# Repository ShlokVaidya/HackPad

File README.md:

# HackPad

A 12-key macropad I built as my second hardware project for Stasis, designed to pair with my 60% keyboard for editing, shortcuts, media control, etc...

Hi there, this is my fully custom keypad from scratch, and I tried to keep it clean, practical, and actually buildable.

## Demo Video

<video src="./HackPad.mp4" controls width="1080">
  Your browser does not support embedded videos. You can watch the demo here: <a href="./HackPad.mp4">HackPad.mp4</a>.
</video>

[Open the demo video](./HackPad.mp4)

Note: The demo vid is working but u need to download to view it as it exceeds the 100mb Github limit. 

## Quick Project Summary

- Project: 3x4 macropad + rotary encoder
- MCU: RP2040 Zero
- Switches: 12x MX-style
- Extra input: 1x EC11 rotary encoder with push switch
- Matrix: 3 rows x 4 columns
- PCB size target: about 100mm x 65mm
- Case workflow: KiCad PCB export -> Onshape assembly -> custom bottom case + plate

## Why I Made This

I wanted a dedicated macropad next to my keyboard for common shortcuts (copy/paste, app switching, media, timeline scrubbing, etc.) and I wanted to learn the full flow:

1. keyboard layout planning
2. schematic capture
3. PCB routing
4. case CAD around real board geometry

## Features

- 12 programmable keys (MX style)
- Rotary encoder with click for volume/scroll/tool size/etc.
- RP2040-based and easy to firmware-program
- Through-hole diodes for matrix
- UART header exposed
- Custom silkscreen logos for personality

## Bill of Materials (BOM)

From [production/bom.csv](production/bom.csv):

| Item | Qty | Notes |
|---|---:|---|
| RP2040 Zero module | 1 | Main controller |
| MX-style switches | 12 | 1u keys |
| 1N4148 diodes | 12 | Matrix diodes |
| EC11 rotary encoder (with switch) | 1 | Knob + click |
| 1x4 right-angle pin header | 1 | UART / expansion |

## Design Files Included

- Schematic: [PCB/HackPad.kicad_sch](PCB/HackPad.kicad_sch)
- PCB: [PCB/HackPad.kicad_pcb](PCB/HackPad.kicad_pcb)
- KiCad project: [PCB/HackPad.kicad_pro](PCB/HackPad.kicad_pro)
- Layout JSON: [PCB/keyboard-layout.json](PCB/keyboard-layout.json)
- Plate DXF: [PCB/plate.dxf](PCB/plate.dxf)
- CAD model: [CAD/HackPad.step](CAD/HackPad.step)
- Production files:
	- [production/bom.csv](production/bom.csv)
	- [production/positions.csv](production/positions.csv)
	- [production/designators.csv](production/designators.csv)
	- [production/netlist.ipc](production/netlist.ipc)

## Firmware

KMK firmware for this board is included in:

- [firmware/kmk/code.py](firmware/kmk/code.py)
- [firmware/kmk/README.md](firmware/kmk/README.md)

It is preconfigured for the exact matrix and encoder pins used in this PCB.

## Progress Pictures

### Research

### Schematic Stage

### PCB Stage

### CAD / Case Stage

## Time Spent (from Journal)

- Research: ~0.33h
- Schematic: ~2.25h
- PCB: ~3.25h
- CAD: ~3.45h

Total logged so far: ~9.3h

## What I Learned

- Importing the actual PCB into CAD early saves a lot of pain later.
- Matrix labeling in schematic makes routing way less confusing.
- Tiny mechanical details (insert depth, nut traps, plate thickness) matter a lot more than expected.
- Silkscreen art is optional, but morale is not.

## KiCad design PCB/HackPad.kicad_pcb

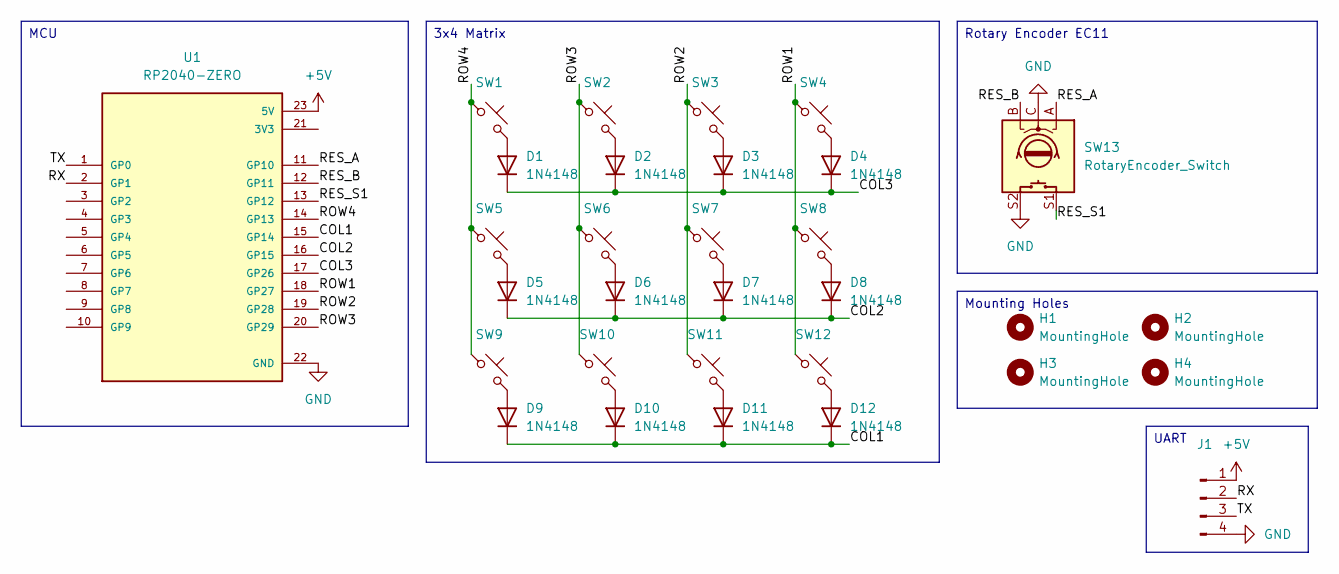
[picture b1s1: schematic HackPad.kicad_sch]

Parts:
D1, D2, D3, D4, D5, D6, D7, D8, D9, D10, D11, D12: 1N4148; D_DO-35_SOD27_P7.62mm_Horizontal
H1, H2, H3, H4: MountingHole; MountingHole_2.7mm_M2.5
J1: Conn_01x04_Pin; PinHeader_1x04_P2.54mm_Horizontal
SW1, SW2, SW3, SW4, SW5, SW6, SW7, SW8, SW9, SW10, SW11, SW12: SW_Push_45deg; SW_MX_HS_KS-2P02B01-01_1u
SW13: RotaryEncoder_Switch; RotaryEncoder_Alps_EC11E-Switch_Vertical_H20mm_MountingHoles
U1: RP2040-ZERO; MODULE_RP2040-ZERO; PARTREV NA

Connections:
+5V: J1.1, U1.23 (5V)
/COL1: D9.1 (K), D10.1 (K), D11.1 (K), D12.1 (K), U1.15 (GP14)
/COL2: D5.1 (K), D6.1 (K), D7.1 (K), D8.1 (K), U1.16 (GP15)
/COL3: D1.1 (K), D2.1 (K), D3.1 (K), D4.1 (K), U1.17 (GP26)
/RES_A: SW13.A, U1.11 (GP10)
/RES_B: SW13.B, U1.12 (GP11)
/RES_S1: SW13.S1, U1.13 (GP12)
/ROW1: SW4.1, SW8.1, SW12.1, U1.18 (GP27)
/ROW2: SW3.1, SW7.1, SW11.1, U1.19 (GP28)
/ROW3: SW2.1, SW6.1, SW10.1, U1.20 (GP29)
/ROW4: SW1.1, SW5.1, SW9.1, U1.14 (GP13)
/RX: J1.2, U1.2 (GP1)
/TX: J1.3, U1.1 (GP0)
GND: J1.4, SW13.C, SW13.S2, U1.22 (GND)
unnamed: D1.2 (A), SW1.2
unnamed: D2.2 (A), SW2.2
unnamed: D3.2 (A), SW3.2
unnamed: D4.2 (A), SW4.2
unnamed: D5.2 (A), SW5.2
unnamed: D6.2 (A), SW6.2
unnamed: D7.2 (A), SW7.2
unnamed: D8.2 (A), SW8.2
unnamed: D9.2 (A), SW9.2
unnamed: D10.2 (A), SW10.2
unnamed: D11.2 (A), SW11.2
unnamed: D12.2 (A), SW12.2

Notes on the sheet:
MCU
Mounting Holes
3x4 Matrix
UART
Rotary Encoder EC11

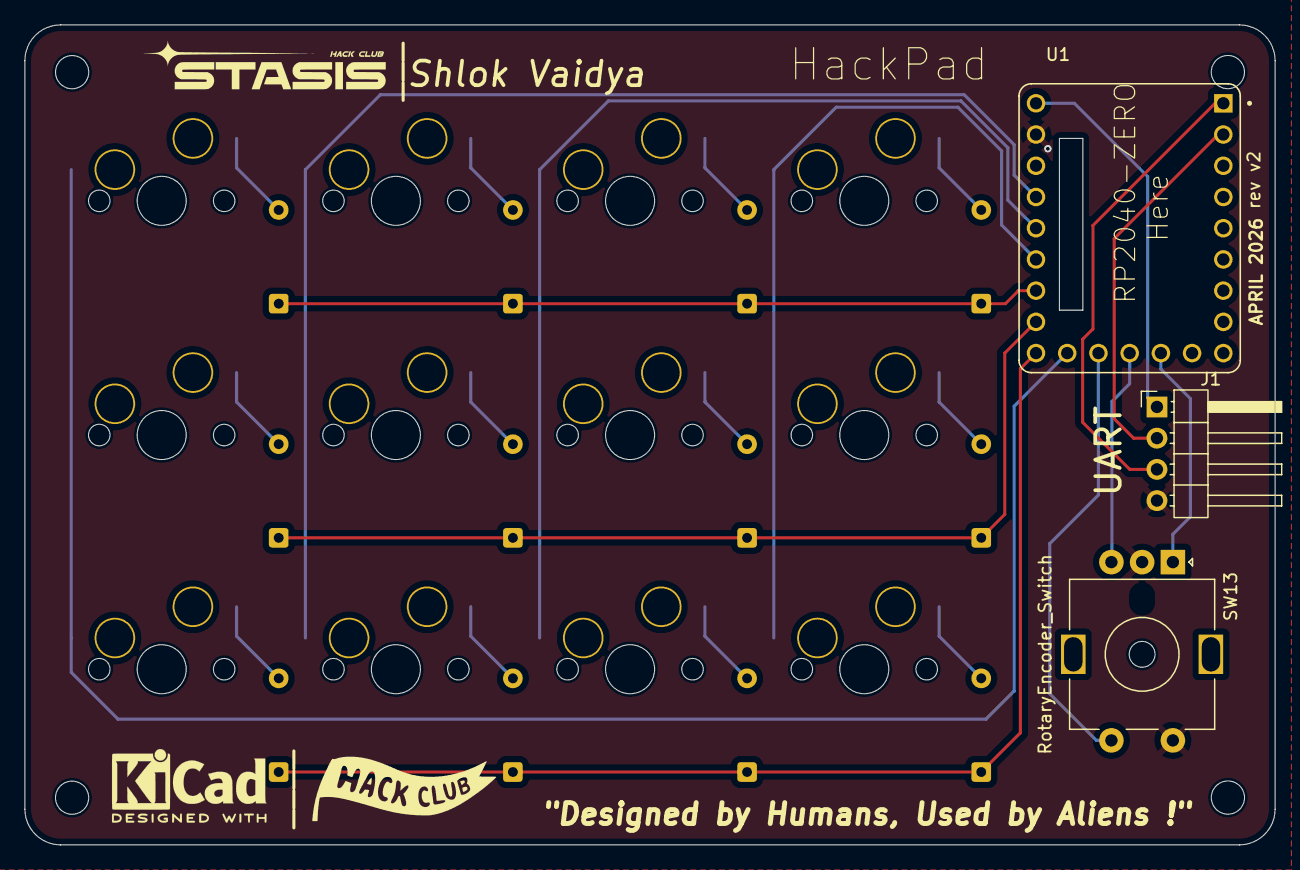
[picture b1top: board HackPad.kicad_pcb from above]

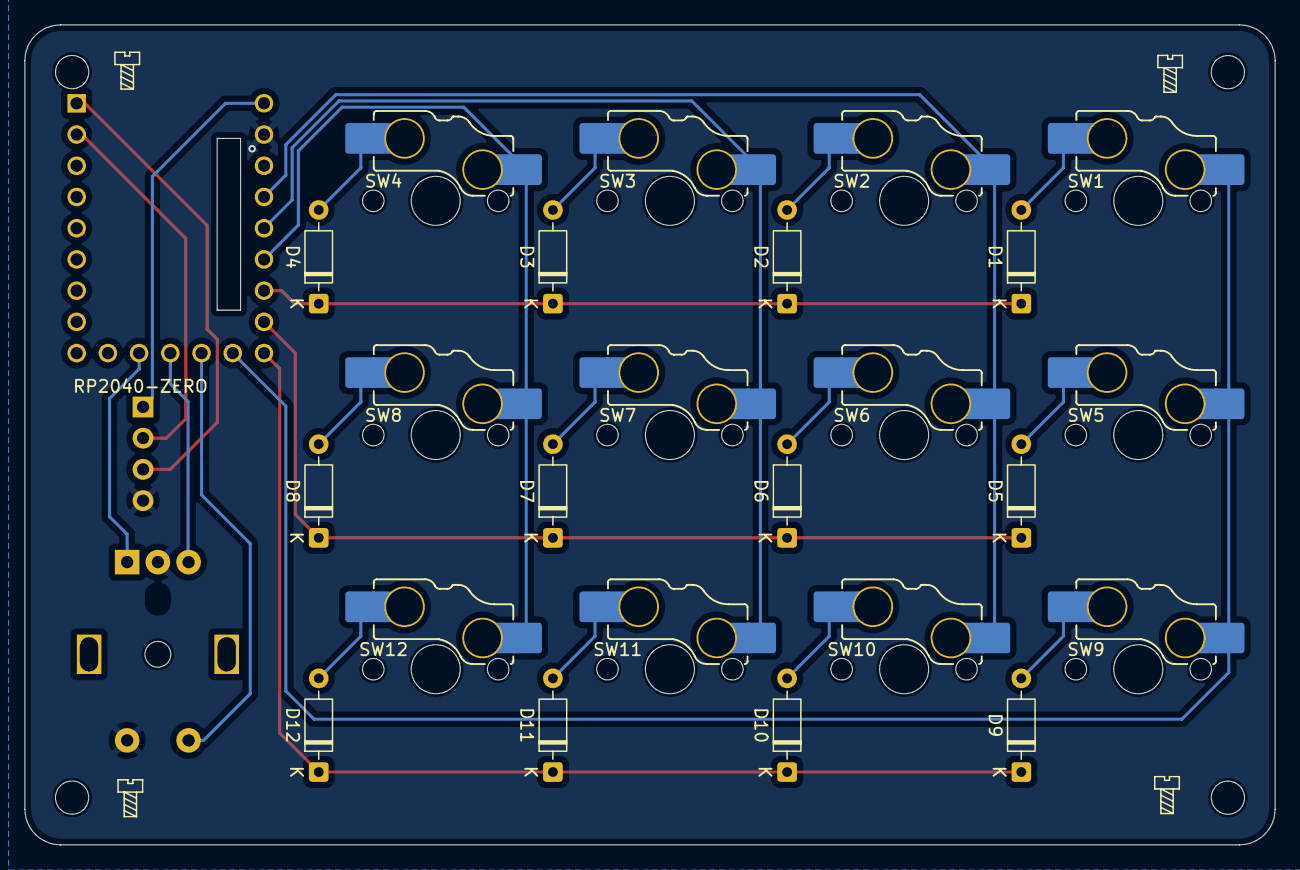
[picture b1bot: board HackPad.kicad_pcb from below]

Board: 2 copper layers, 101.7 x 66.7 mm, 33 parts (24 on the bottom side), 26 nets.

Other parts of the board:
H: MountingHole; MountingHole_2.7mm_M2.5
Pogo: LOGO; HackClub

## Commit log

2026-04-05 v2.1
2026-04-05 added Firmware
2026-06-21 Added Demo vid
2026-06-21 Added note on demo vid
